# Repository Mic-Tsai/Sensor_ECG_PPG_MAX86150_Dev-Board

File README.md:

## Sensor_ECG_PPG_MAX86150 | Dev-Board

Arduino based sensor learning project. The feature combines ECG/PPG data with heart rate calculation, plotting the ECG/PPG curve which used Processing on your computer.

 - Bias Cancellation | Store raw data in time, when new data coming that bias level will calculate as hysteresis filter.

 - Heart Rate Detect | Setting upper/lower threshold once your ECG/PPG value cross u/l threshold, check windows will output the BPM results (Both PPG/ECG).

##

### Wireless Support ###

This board also support WiFi transmission via ESPNOW (ESP8266 Broadcast), and need power by battery. And you need 2x esp8266 board.

1) Read receiver esp8266's mac address.
2) Fill it into the transmitter sketch. "ECG_PPG_MAX86150_V5_WiFi_TX"

**A Known Issue**

Sampling rate from MAX86150 set as 200sps, but ESP8266's multiplex with ESP-NOW and sensor hub reading task, it will low down the output sample rate to ~150sps. So, when you measuring your ECG/PPG in real-time plot, it may show the missing R-R interval. (R-peak missing!) Don't worry it just the lower sample rate caused.

```
Arduino tool kit, and require the following material:
- MCU: ESP8266 
- Display: SD1306_128x64_OLED
- Sensor: MAX86150
```
##

For coding example, you need the following library:

* [Adafruit_SSD1306](https://github.com/adafruit/Adafruit_SSD1306)
* [protocentral_max86150_ecg_ppg](https://github.com/Protocentral/protocentral_max86150_ecg_ppg)

## 

Any question or need technical support:

* Contact me via mail (xbcke12345@gmail.com)
* If this project helping. Please generously support =)

## 

## 

>### License Information
>>This product is open source! Both, our hardware and software are open source and licensed under the following:
>>#### Hardware
>>>All hardware is released under [Creative Commons Share-alike 4.0 International](http://creativecommons.org/licenses/by-sa/4.0/)
>>#### Software 
>>>All software is released under the MIT License [http://opensource.org/licenses/MIT](http://opensource.org/licenses/MIT)
>>#### Documentation
>>>The documentation on this page is released under [Creative Commons Share-alike 4.0 International](http://creativecommons.org/licenses/by-sa/4.0/)

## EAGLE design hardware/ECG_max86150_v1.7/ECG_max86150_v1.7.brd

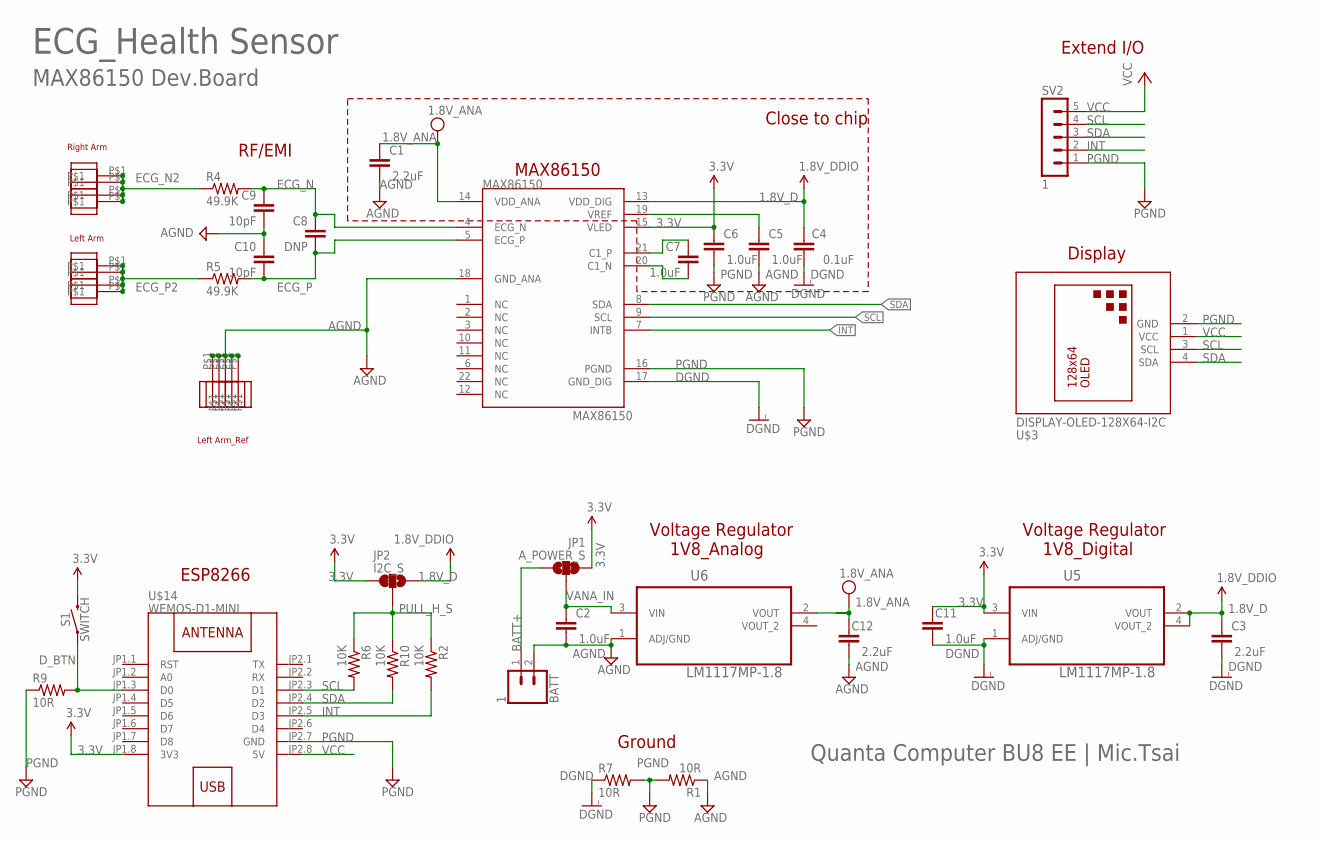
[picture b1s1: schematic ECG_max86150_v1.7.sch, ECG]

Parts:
BATT: 1; 1X02
C1, C3, C12: 2.2uF; 0805
C2, C5, C6, C7, C11: 1.0uF; 0805
C4: 0.1uF; 0402
C8: DNP; 0402
C9, C10: 10pF; 0402
JP1: A_POWER_S; SMT-JUMPER_3_1-NC_TRACE_SILK
JP2: I2C_S; SMT-JUMPER_3_1-NC_TRACE_SILK
MAX86150: MAX86150
R1, R7, R9: 10R; 0805
R2, R6, R10: 10K; 0402-RES
R4, R5: 49.9K; 0402-RES
S1: SWITCH; TACTILE_SWITCH_PTH_6.0MM
SV2: 1; MA05-1
U5, U6: LM1117MP-1.8; SOT230P696X180-4N
U$1, U$4, U$6, U$7, U$9, U$10, U$11, U$12, U$13, U$15, U$16, U$17, U$18: ECG_PAD; ECG_PAD1
U$3: DISPLAY-OLED-128X64-I2C
U$14: WEMOS-D1-MINI

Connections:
1.8V_ANA: C1.1, C12.1, MAX86150.14 (VDD_ANA), U6.2 (VOUT)
1.8V_D: C3.1, C4.1, JP2.1, MAX86150.13 (VDD_DIG), U5.2 (VOUT), U5.4 (VOUT_2)
3.3V: C6.1, C11.1, JP1.3, JP2.3, MAX86150.15 (VLED), S1.3 (2), U5.3 (VIN), U$14.JP1.8 (3V3)
AGND: BATT.2, C1.2, C2.2, C5.2, C9.2, C10.1, C12.2, MAX86150.18 (GND_ANA), R1.1, U6.1 (ADJ/GND), U$12.P$1, U$13.P$1, U$15.P$1, U$17.P$1, U$18.P$1
BATT+: BATT.1, JP1.1
DGND: C3.2, C4.2, C11.2, MAX86150.17 (GND_DIG), R7.1, U5.1 (ADJ/GND)
D_BTN: R9.2, S1.1, U$14.JP1.3 (D0)
ECG_N: C8.1, C9.1, MAX86150.4 (ECG_N), R4.2
ECG_N2: R4.1, U$9.P$1, U$10.P$1, U$11.P$1, U$16.P$1
ECG_P: C8.2, C10.2, MAX86150.5 (ECG_P), R5.2
ECG_P2: R5.1, U$1.P$1, U$4.P$1, U$6.P$1, U$7.P$1
INT: MAX86150.7 (INTB), R2.2, SV2.2, U$14.JP2.5 (D3)
unnamed: C7.1, MAX86150.21 (C1_P)
unnamed: C7.2, MAX86150.20 (C1_N)
unnamed: C5.1, MAX86150.19 (VREF)
PGND: C6.2, MAX86150.16 (PGND), R1.2, R7.2, R9.1, SV2.1, U$3.2 (GND), U$14.JP2.7 (GND)
PULL_H_S: JP2.2, R2.1, R6.1, R10.1
SCL: MAX86150.9 (SCL), R6.2, SV2.4, U$3.3 (SCL), U$14.JP2.3 (D1)
SDA: MAX86150.8 (SDA), R10.2, SV2.3, U$3.4 (SDA), U$14.JP2.4 (D2)
VANA_IN: C2.1, JP1.2, U6.3 (VIN)
VCC: SV2.5, U$3.1 (VCC), U$14.JP2.8 (5V)

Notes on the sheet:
Close to chip
ECG_Health Sensor
MAX86150 Dev.Board
Quanta Computer BU8 EE | Mic.Tsai
Left Arm
RF/EMI
Ground
Right Arm
Left Arm_Ref
Voltage Regulator 1V8_Analog
Voltage Regulator 1V8_Digital
Extend I/O
MAX86150
ESP8266
Display

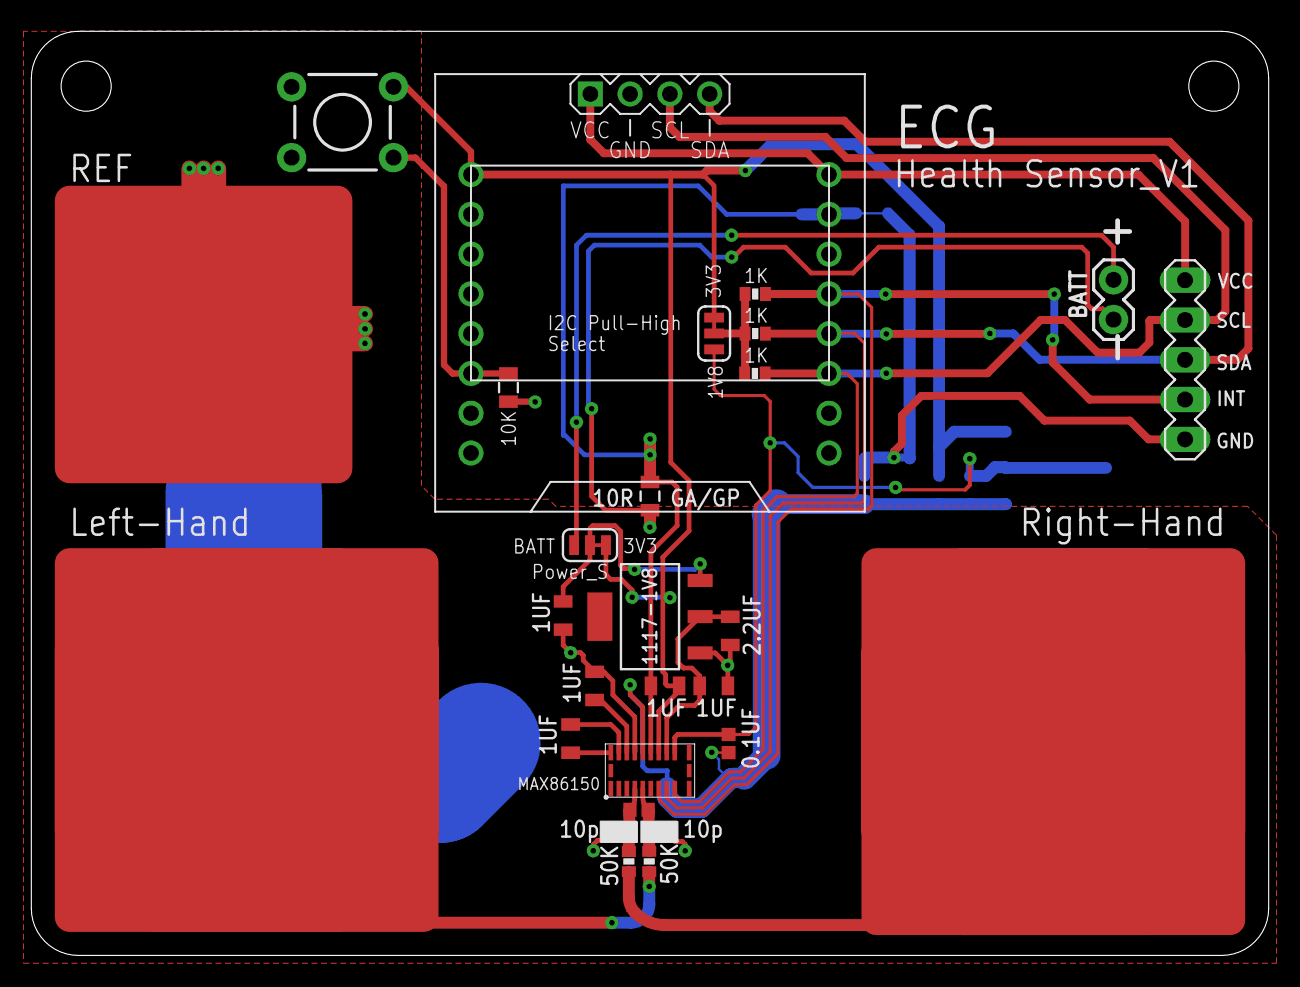
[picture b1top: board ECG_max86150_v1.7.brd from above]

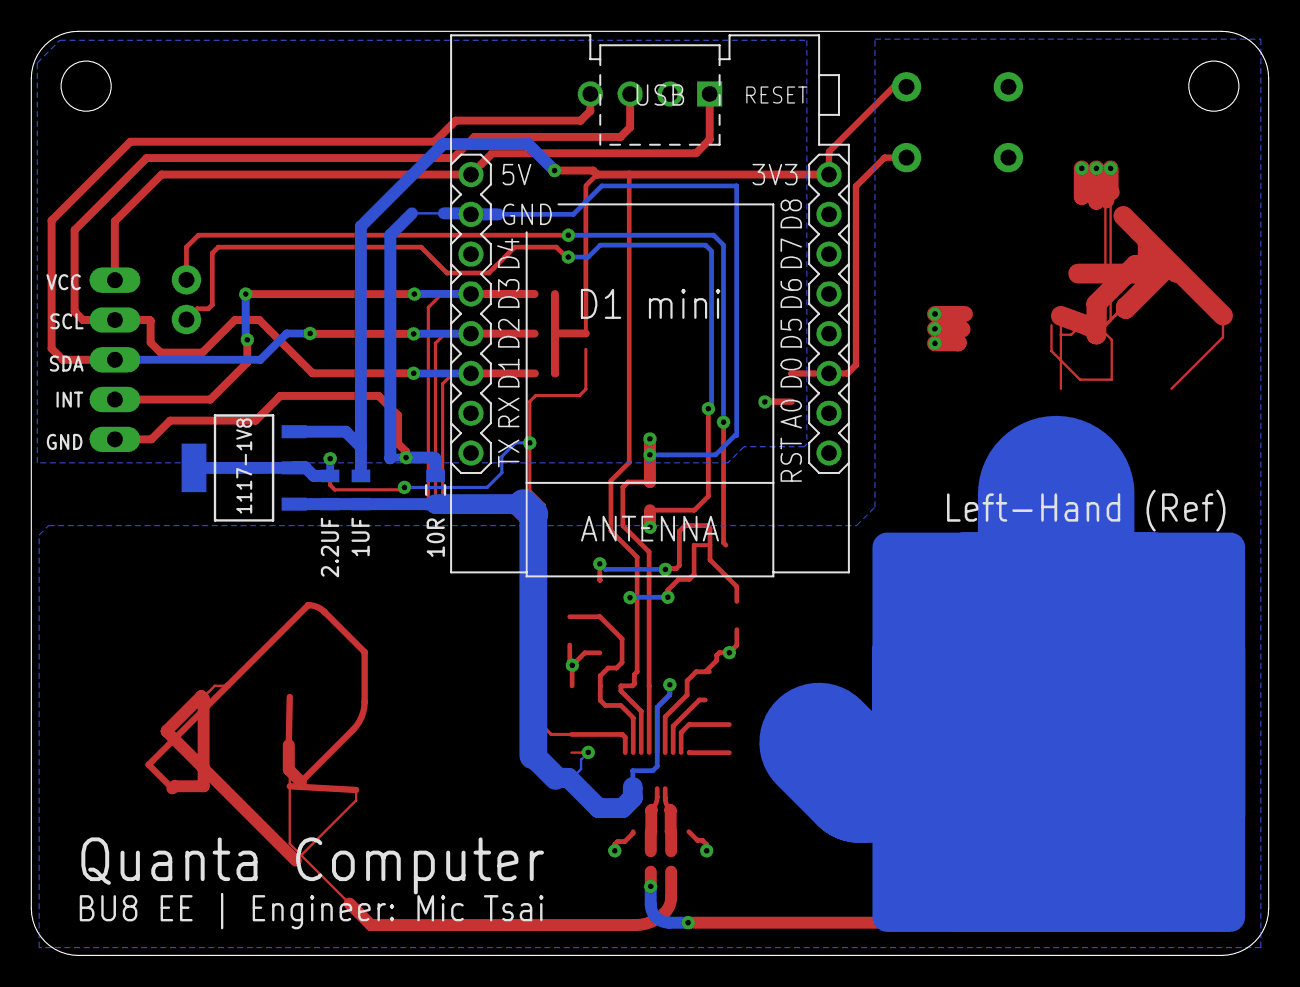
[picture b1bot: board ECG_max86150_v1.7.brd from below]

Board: 2 copper layers, 79.0 x 59.0 mm, 43 parts (9 on the bottom side), 21 nets.

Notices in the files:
parts and their libraries:
SparkFun-Capacitors: Licensing: Creative Commons ShareAlike 4.0 International - https://creativecommons.org/licenses/by-sa/4.0
diy-modules: Released under the Creative Commons Attribution 4.0 International License: http://creativecommons.org/licenses/by/4.0
